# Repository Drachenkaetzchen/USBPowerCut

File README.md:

# USB Power Cut

A small PCB to control power to a USB device. I've designed this in order to be able to cut power to a
[HDMI display](https://www.aliexpress.com/item/32889893278.html) when it's not in use, for example, via a Raspberry Pi.

# Specifications

- MicroUSB input
- USB Type A output
- Maximum permissible USB current draw: 1A
- JST XH to control the power. Control voltage 3.3V or 5V.
- Active power consumption 35mA (only when switched on)

# Known Issues

- One mounting hole is offset to the right by 0.5mm, the DIN mounting adapter is adjusted for that.

# BOM

| Designator| Part
| ----------|--------------------
| D1 | 1N4148 DO35-10                   
| K1 | V23079-A1011-B301                   
| Q1 | 2N7002 SOT23                     
| R1 | 100k 0805                     
| X1 | JST XH 2 pin
| X2 | AMP 787616-1                       
| X3 | 10104110-0001LF                 

# FAQ

**Why a relay?**

I didn't have any P-channel mosfets in stock, but plenty of those small relays, so that's why I based my design around
them. I rather use components I have in stock than to order new ones.

N-channel mosfets shouldn't be used to control USB power due to possible leakage over the data lines.

**Why not use the RPI4 USB power control functionality?**

On a Raspberry Pi 4, this cuts power to all USB ports. In my case, I only want the display to be turned off. All other
ports should remain on.

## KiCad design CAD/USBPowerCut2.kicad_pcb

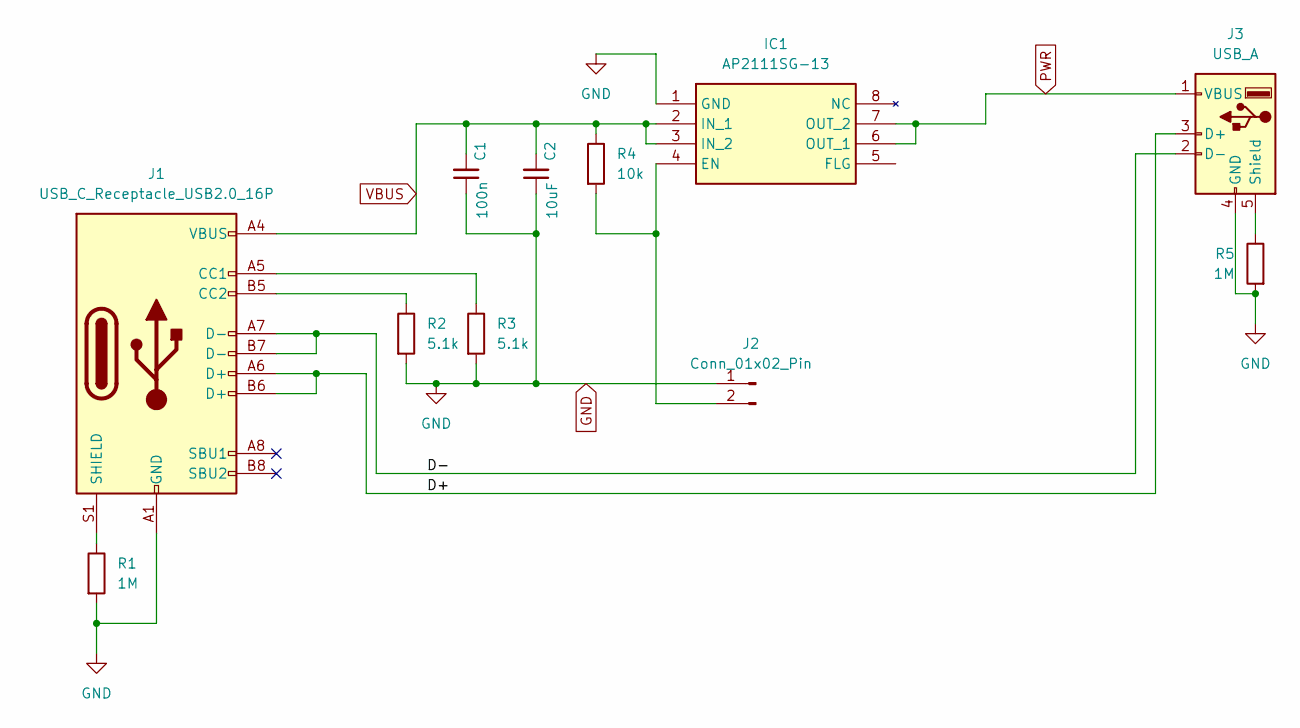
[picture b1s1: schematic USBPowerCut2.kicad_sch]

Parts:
C1: 100n; C_0603_1608Metric; LCSC C14663
C2: 10uF; C_0603_1608Metric; LCSC C19702
IC1: AP2111SG-13; SOIC127P600X175-8N; Manufacturer_Part_Number AP2111SG-13; Mouser Part Number 621-AP2111SG-13
J1: USB_C_Receptacle_USB2.0_16P; USB_C_Receptacle_HRO_TYPE-C-31-M-12; LCSC C2988369
J2: Conn_01x02_Pin; JST_PH_B2B-PH-K_1x02_P2.00mm_Vertical
J3: USB_A; USB_A_CONNFLY_DS1095-WNR0; LCSC C19944603
R1, R5: 1M; R_0603_1608Metric; LCSC C22935
R2, R3: 5.1k; R_0603_1608Metric; LCSC C23186
R4: 10k; R_0603_1608Metric; LCSC C25804

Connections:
/D+: J1.A6 (D+), J1.B6 (D+), J3.3 (D+)
/D-: J1.A7 (D-), J1.B7 (D-), J3.2 (D-)
GND: C1.1, C2.1, IC1.1 (GND), J1.A1 (GND), J1.A12 (GND), J1.B1 (GND), J1.B12 (GND), J2.1, J3.4 (GND), R1.2, R2.2, R3.2, R5.2
unnamed: IC1.4 (EN), J2.2, R4.2
unnamed: J1.A5 (CC1), R3.1
unnamed: J1.B5 (CC2), R2.1
unnamed: J1.S1 (SHIELD), R1.1
unnamed: J3.5 (Shield), R5.1
PWR: IC1.6 (OUT_1), IC1.7 (OUT_2), J3.1 (VBUS)
VBUS: C1.2, C2.2, IC1.2 (IN_1), IC1.3 (IN_2), J1.A4 (VBUS), J1.A9 (VBUS), J1.B4 (VBUS), J1.B9 (VBUS), R4.1

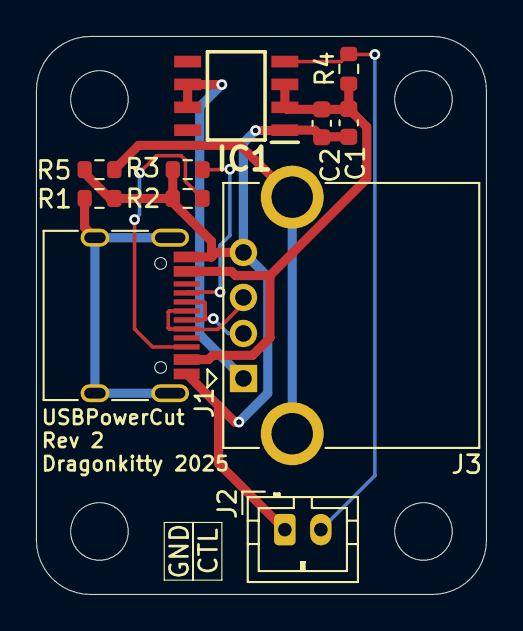
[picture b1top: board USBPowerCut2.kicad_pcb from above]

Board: 2 copper layers, 25.0 x 31.0 mm, 11 parts (0 on the bottom side), 10 nets.

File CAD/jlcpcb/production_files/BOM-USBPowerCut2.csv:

Comment,Designator,Footprint,LCSC,Quantity
Conn_01x02_Pin,J2,JST_PH_B2B-PH-K_1x02_P2.00mm_Vertical,C131337,1
100n,C1,C_0603_1608Metric,C14663,1
AP2111SG-13,IC1,SOIC127P600X175-8N,C151559,1
10uF,C2,C_0603_1608Metric,C19702,1
USB_A,J3,USB_A_CONNFLY_DS1095-WNR0,C19944603,1
1M,"R1,R5",R_0603_1608Metric,C22935,2
5.1k,"R2,R3",R_0603_1608Metric,C23186,2
10k,R4,R_0603_1608Metric,C25804,1
USB_C_Receptacle_USB2.0_16P,J1,USB_C_Receptacle_HRO_TYPE-C-31-M-12,C2988369,1

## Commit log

2021-10-18 Clarified that the data lines are passed through
2025-02-01 Prepare repo for V2
2025-03-20 Updated docs
